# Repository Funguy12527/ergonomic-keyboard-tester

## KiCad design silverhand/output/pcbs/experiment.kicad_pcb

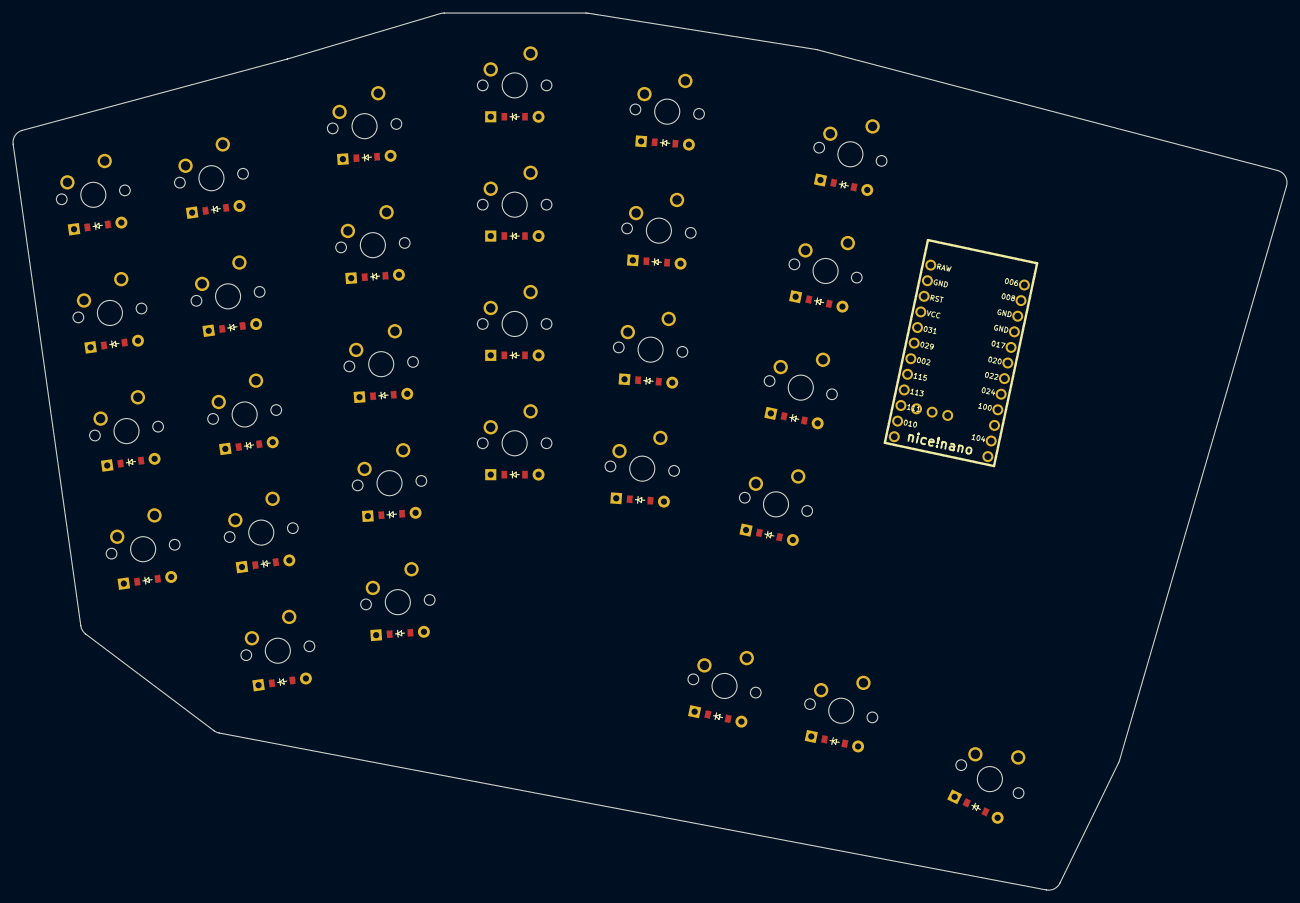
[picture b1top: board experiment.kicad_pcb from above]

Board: 2 copper layers, 202.9 x 139.7 mm, 59 parts (0 on the bottom side), 36 nets, no tracks yet.

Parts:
D1, D2, D3, D4, D5, D6, D7, D8, D9, D10, D11, D12, D13, D14, D15, D16, D17, D18, D19, D20, D21, D22, D23, D24, D25, D26, D27, D28, D29: ComboDiode
MCU1: nice_nano
S1, S2, S3, S4, S5, S6, S7, S8, S9, S10, S11, S12, S13, S14, S15, S16, S17, S18, S19, S20, S21, S22, S23, S24, S25, S26, S27, S28, S29: MX

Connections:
GND: MCU1.3, MCU1.4, MCU1.23
P009: MCU1.13, S23.1, S24.1, S25.1, S26.1, S29.1
P011: MCU1.10, S10.1, S11.1, S12.1, S13.1, S14.1
P024: MCU1.8, S1.1, S2.1, S3.1, S4.1
P100: MCU1.9, S5.1, S6.1, S7.1, S8.1, S9.1
P104: MCU1.11, S15.1, S16.1, S17.1, S18.1, S27.1
P106: MCU1.12, S19.1, S20.1, S21.1, S22.1, S28.1
index_home: D20.2, S20.2
index_low: D19.2, S19.2
index_nums: D22.2, S22.2
index_top: D21.2, S21.2
indexfar_home: D24.2, S24.2
indexfar_low: D23.2, S23.2
indexfar_nums: D26.2, S26.2
indexfar_top: D25.2, S25.2
layer1_layerkey: D28.2, S28.2
layer2_layerkey: D27.2, S27.2
middle_home: D16.2, S16.2
middle_low: D15.2, S15.2
middle_nums: D18.2, S18.2
middle_top: D17.2, S17.2
pinky_home: D7.2, S7.2
pinky_low: D6.2, S6.2
pinky_mod: D5.2, S5.2
pinky_nums: D9.2, S9.2
pinky_top: D8.2, S8.2
pinkyfar_home: D2.2, S2.2
pinkyfar_low: D1.2, S1.2
pinkyfar_nums: D4.2, S4.2
pinkyfar_top: D3.2, S3.2
ring_home: D12.2, S12.2
ring_low: D11.2, S11.2
ring_mod: D10.2, S10.2
ring_nums: D14.2, S14.2
ring_top: D13.2, S13.2
space_layerkey: D29.2, S29.2

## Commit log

2025-05-17 5.18 finished basic key layout
2025-05-17 board outline #1generated
2025-05-17 changed board
2025-05-17 add spread
2025-05-18 PCB Design
